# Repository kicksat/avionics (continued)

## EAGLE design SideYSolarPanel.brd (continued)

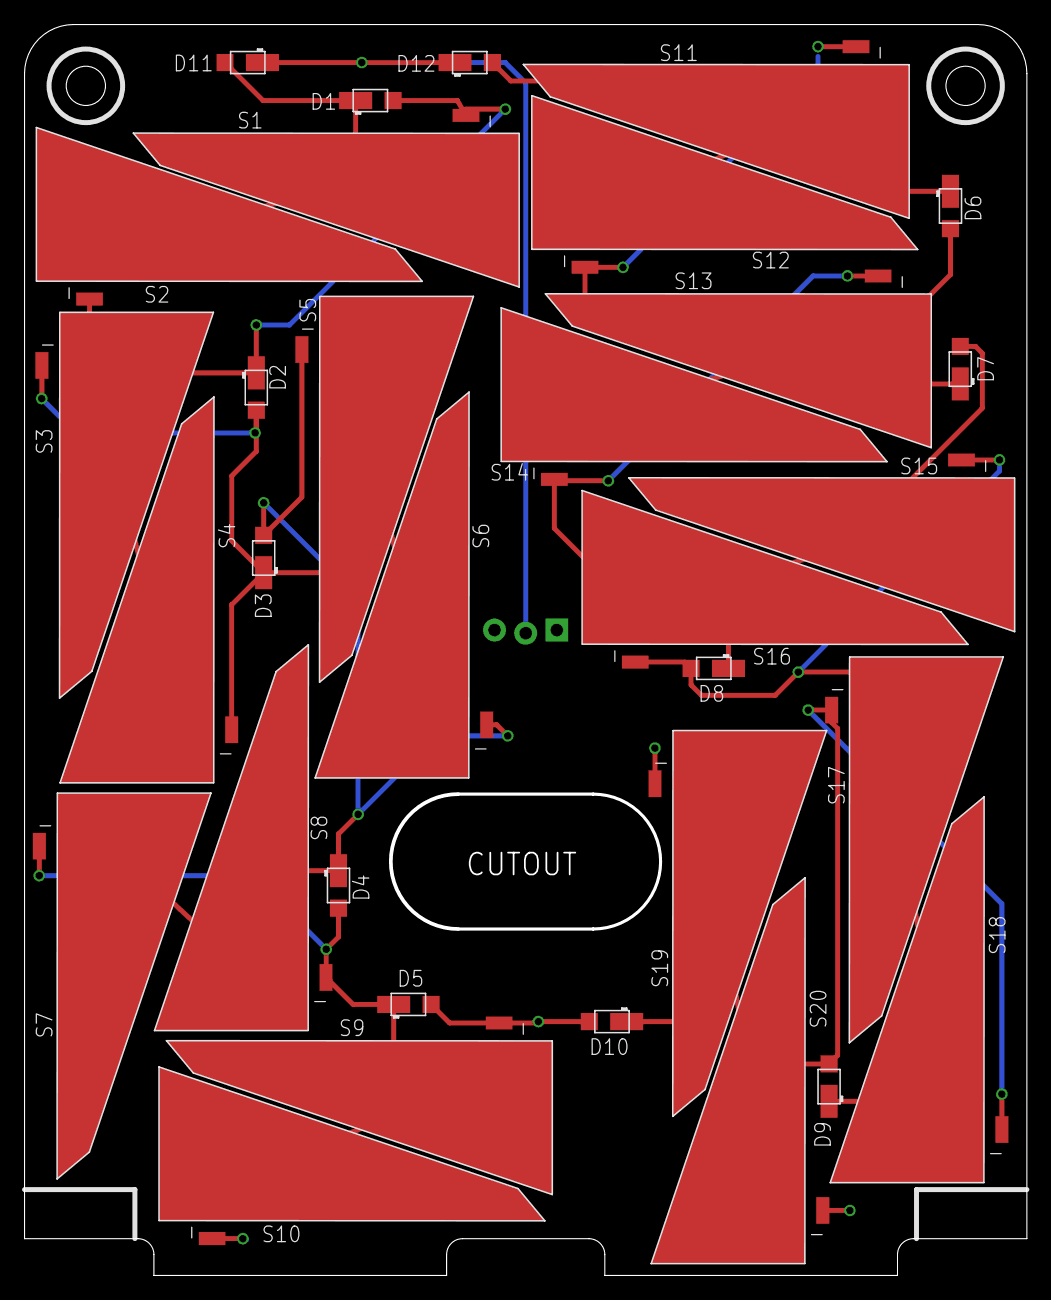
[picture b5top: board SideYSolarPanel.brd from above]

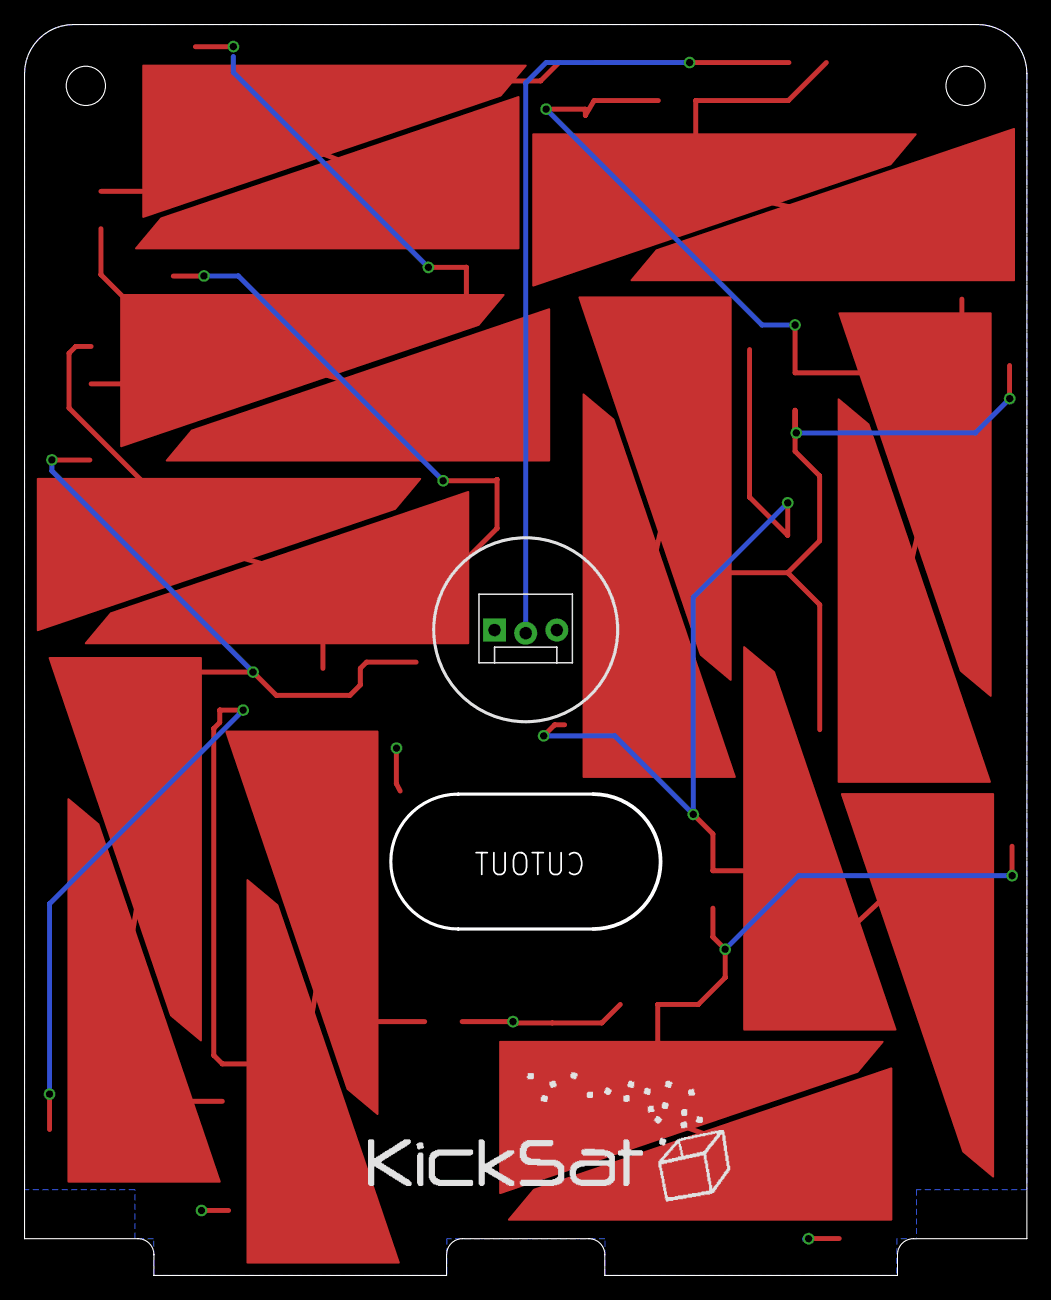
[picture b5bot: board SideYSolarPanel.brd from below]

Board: 2 copper layers, 81.7 x 102.0 mm, 35 parts (2 on the bottom side), 12 nets.

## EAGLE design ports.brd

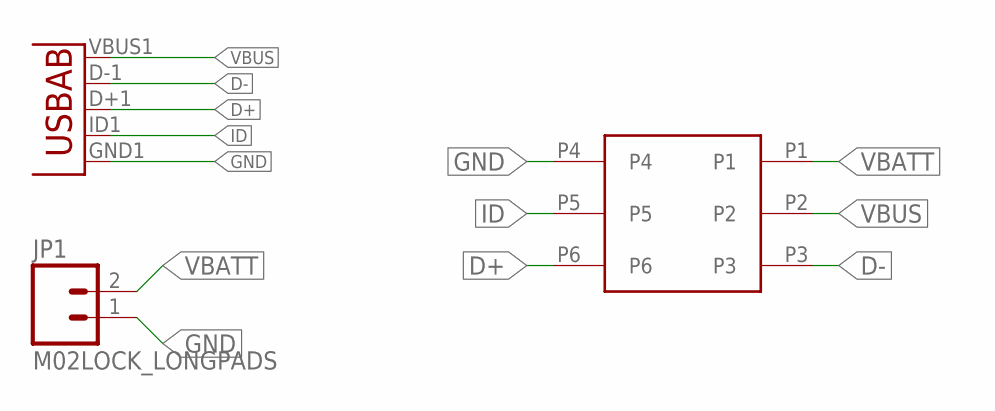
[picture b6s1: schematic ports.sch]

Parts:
JP1: M02LOCK_LONGPADS; 1X02_LOCK_LONGPADS
U$1: G125-FV20605L0P
U$4: USB-AB""; USB-AB-MICRO-SMD_V02_BOSS

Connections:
D+: U$1.P6, U$4.D+1 (D+)
D-: U$1.P3, U$4.D-1 (D-)
GND: JP1.1, U$1.P4, U$4.GND1 (GND)
ID: U$1.P5, U$4.ID1 (USBID)
VBATT: JP1.2, U$1.P1
VBUS: U$1.P2, U$4.VBUS1 (VBUS)

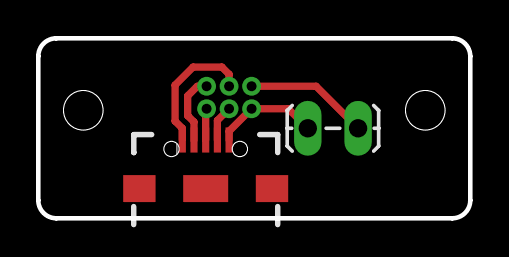
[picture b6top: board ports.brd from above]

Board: 2 copper layers, 24.0 x 10.0 mm, 3 parts (1 on the bottom side), 6 nets.

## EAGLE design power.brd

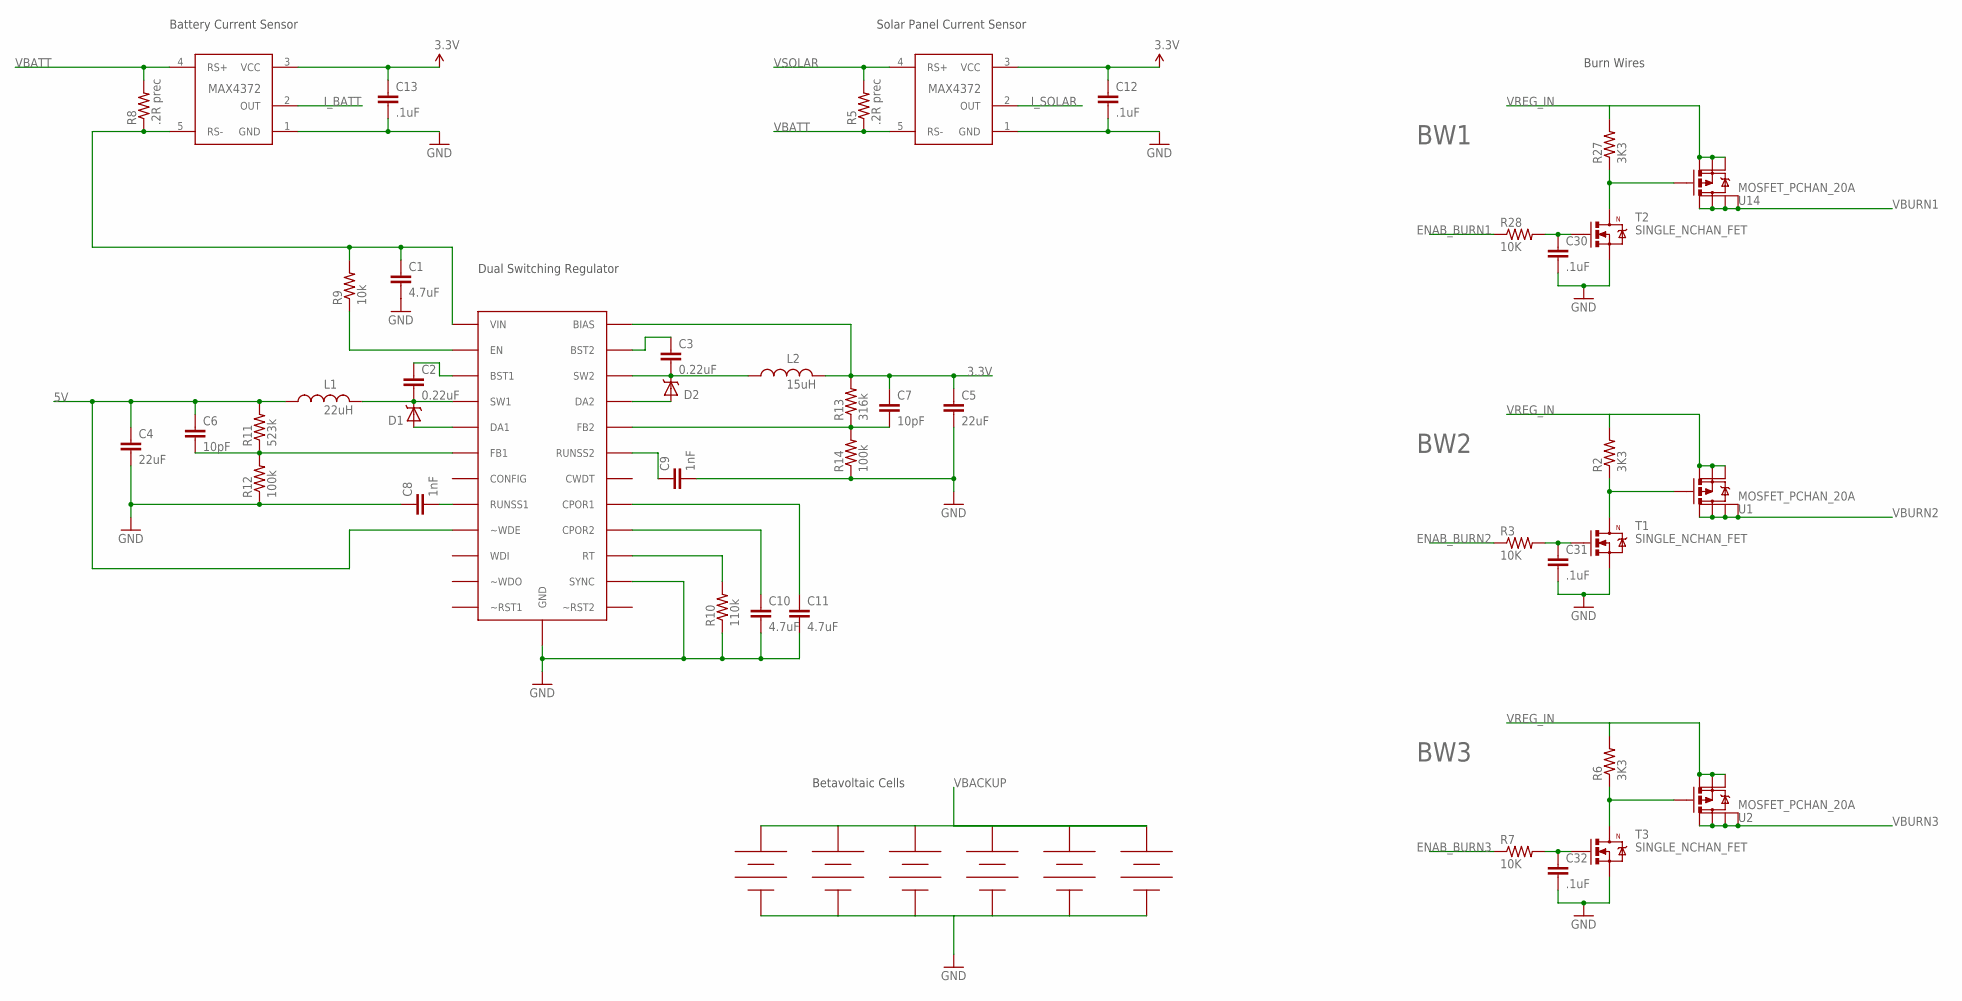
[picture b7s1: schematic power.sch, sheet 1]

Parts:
C1, C10, C11: 4.7uF; 0805
C2, C3: 0.22uF; 0805
C4, C5: 22uF; 1210
C6, C7: 10pF; 0805
C8, C9: 1nF; 0805
C12, C13, C30, C31, C32: .1uF; 0805
D1, D2: BAT20J; SOD-323
L1, L2: SLF10145
R2, R6, R27: 3K3; 0805
R3, R7, R28: 10K; 0805
R5, R8: .2R prec; 0805
R9: 10k; 0805
R10: 110k; 0805
R11: 523k; 0805
R12, R14: 100k; 0805
R13: 316k; 0805
T1, T2, T3: SINGLE_NCHAN_FET; SOT23-3
U1, U2, U14: MOSFET_PCHAN_20A; SO8
U$7, U$8, U$9, U$10, U$11, U$12: BETABATTERY
U$13: LT3688; LT3688TSSOP
U$14, U$15: CURRENT_MAX4372; SOT23-5

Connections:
3.3V: C5.1, C7.1, C12.1, C13.1, L2.P2, R13.2, U$13.BIAS, U$14.3 (VCC), U$15.3 (VCC); also elsewhere on the board
5V: C4.1, C6.1, L1.P1, R11.2, U$13.WDE (~WDE); also elsewhere on the board
ENAB_BURN1: R28.1
ENAB_BURN2: R3.1
ENAB_BURN3: R7.1
GND: C1.2, C4.2, C5.2, C8.1, C9.2, C10.2, C11.2, C12.2, C13.2, C30.2, C31.2, C32.2, R10.1, R12.1, R14.1, T1.2 (S), T2.2 (S), T3.2 (S), U$7.V-, U$8.V-, U$9.V-, U$10.V-, U$11.V-, U$12.V-, U$13.GND, U$13.SYNC, U$14.1 (GND), U$15.1 (GND); also elsewhere on the board
I_BATT: U$15.2 (OUT)
I_SOLAR: U$14.2 (OUT)
unnamed: C31.1, R3.2, T1.1 (G)
unnamed: R2.1, T1.3 (D), U1.4 (G)
unnamed: C32.1, R7.2, T3.1 (G)
unnamed: R6.1, T3.3 (D), U2.4 (G)
unnamed: R9.1, U$13.EN
unnamed: C9.1, U$13.RUNSS2
unnamed: C2.1, U$13.BST1
unnamed: C2.2, D1.C, L1.P2, U$13.SW1
unnamed: C3.1, U$13.BST2
unnamed: C6.2, R11.1, R12.2, U$13.FB1
unnamed: C8.2, U$13.RUNSS1
unnamed: C7.2, R13.1, R14.2, U$13.FB2
unnamed: C3.2, D2.C, L2.P1, U$13.SW2
unnamed: D1.A, U$13.DA1
unnamed: D2.A, U$13.DA2
unnamed: R10.2, U$13.RT
unnamed: C10.1, U$13.CPOR2
unnamed: C30.1, R28.2, T2.1 (G)
unnamed: C11.1, U$13.CPOR1
unnamed: R27.1, T2.3 (D), U14.4 (G)
VBACKUP: U$7.V+, U$8.V+, U$9.V+, U$10.V+, U$11.V+, U$12.V+; also elsewhere on the board
VBATT: R5.1, R8.2, U$14.5 (RS-), U$15.4 (RS+)
VBURN1: U14.5 (D), U14.6 (D), U14.7 (D), U14.8 (D); also elsewhere on the board
VBURN2: U1.5 (D), U1.6 (D), U1.7 (D), U1.8 (D); also elsewhere on the board
VBURN3: U2.5 (D), U2.6 (D), U2.7 (D), U2.8 (D); also elsewhere on the board
VREG_IN: C1.1, R2.2, R6.2, R8.1, R9.2, R27.2, U1.1 (S), U1.2 (S), U1.3 (S), U2.1 (S), U2.2 (S), U2.3 (S), U14.1 (S), U14.2 (S), U14.3 (S), U$13.VIN, U$15.5 (RS-); also elsewhere on the board
VSOLAR: R5.2, U$14.4 (RS+); also elsewhere on the board

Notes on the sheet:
BW1
BW2
BW3
22uH
15uH
Dual Switching Regulator
Betavoltaic Cells
Burn Wires
Solar Panel Current Sensor
Battery Current Sensor

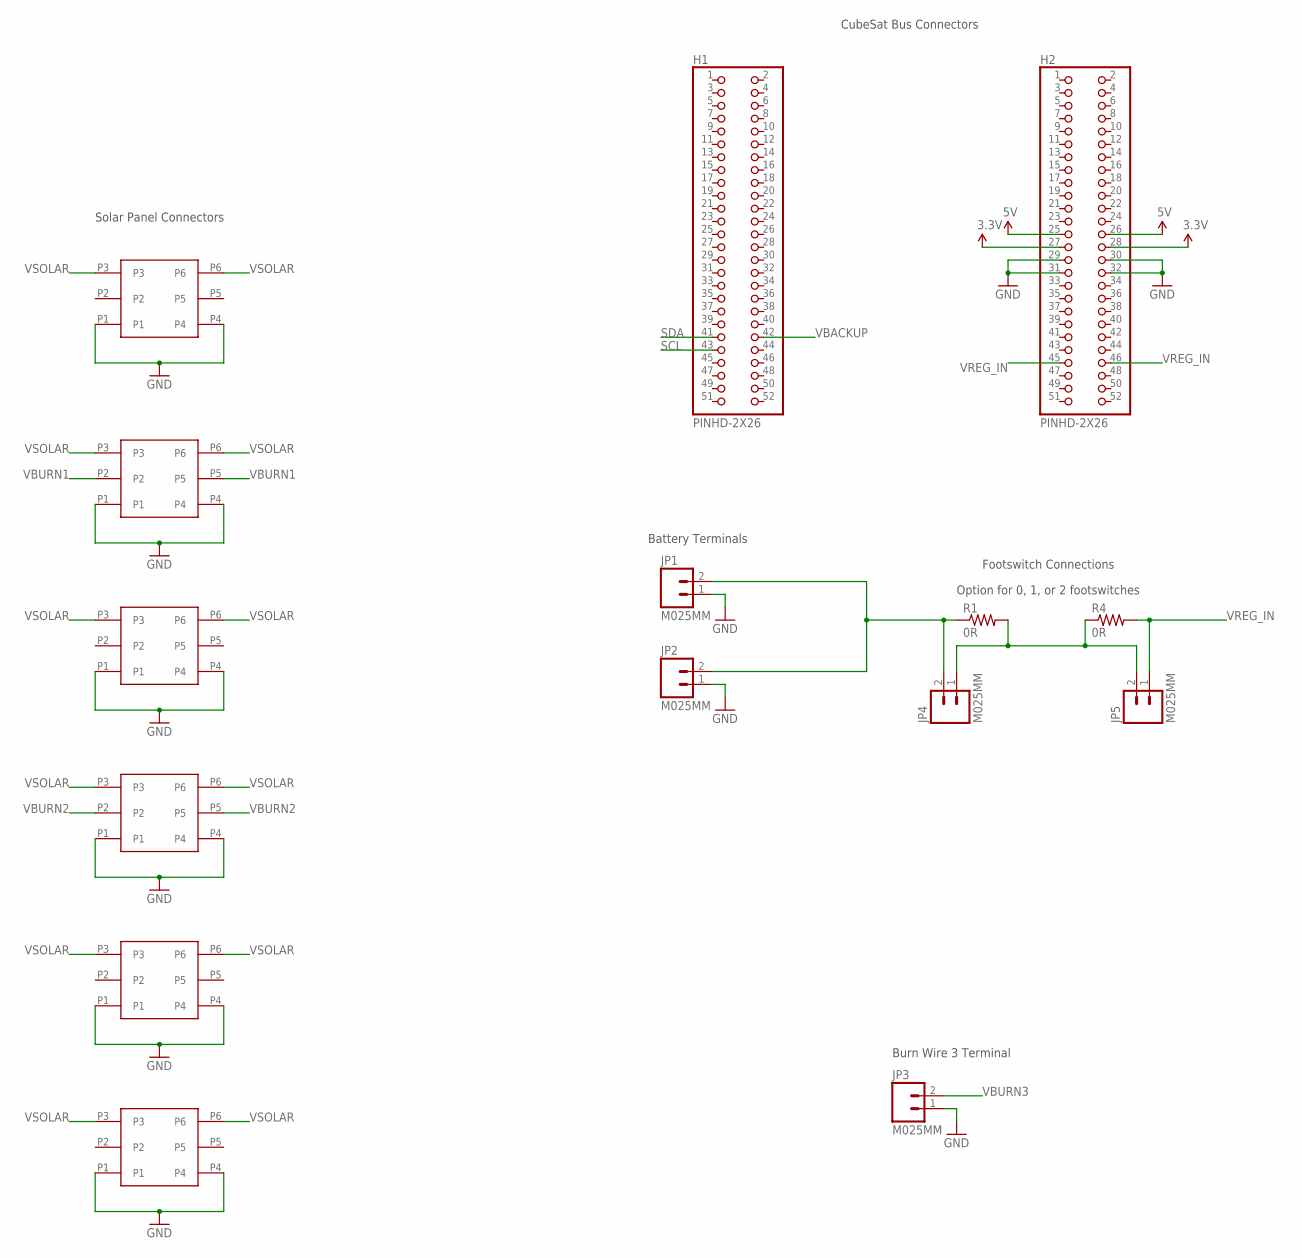
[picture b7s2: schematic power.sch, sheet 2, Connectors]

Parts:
H1, H2: PINHD-2X26; 2X26
JP1, JP2, JP3, JP4, JP5: M025MM; SCREWTERMINAL-5MM-2
R1, R4: 0R; R1210
U$1, U$2, U$3, U$4, U$5, U$6: G125-FV20605L0P

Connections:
3.3V: H2.27, H2.28; also elsewhere on the board
5V: H2.25, H2.26; also elsewhere on the board
BATT_INPUT: JP1.2, JP2.2, JP4.2, R1.1
GND: H2.29, H2.30, H2.31, H2.32, JP1.1, JP2.1, JP3.1, U$1.P1, U$1.P4, U$2.P1, U$2.P4, U$3.P1, U$3.P4, U$4.P1, U$4.P4, U$5.P1, U$5.P4, U$6.P1, U$6.P4; also elsewhere on the board
unnamed: JP4.1, JP5.2, R1.2, R4.1
SCL: H1.43
SDA: H1.41
VBACKUP: H1.42; also elsewhere on the board
VBURN1: U$6.P2, U$6.P5; also elsewhere on the board
VBURN2: U$1.P2, U$1.P5; also elsewhere on the board
VBURN3: JP3.2; also elsewhere on the board
VREG_IN: H2.45, H2.46, JP5.1, R4.2; also elsewhere on the board
VSOLAR: U$1.P3, U$1.P6, U$2.P3, U$2.P6, U$3.P3, U$3.P6, U$4.P3, U$4.P6, U$5.P3, U$5.P6, U$6.P3, U$6.P6; also elsewhere on the board

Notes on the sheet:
Footswitch Connections
Option for 0, 1, or 2 footswitches
Solar Panel Connectors
CubeSat Bus Connectors
Battery Terminals
Burn Wire 3 Terminal

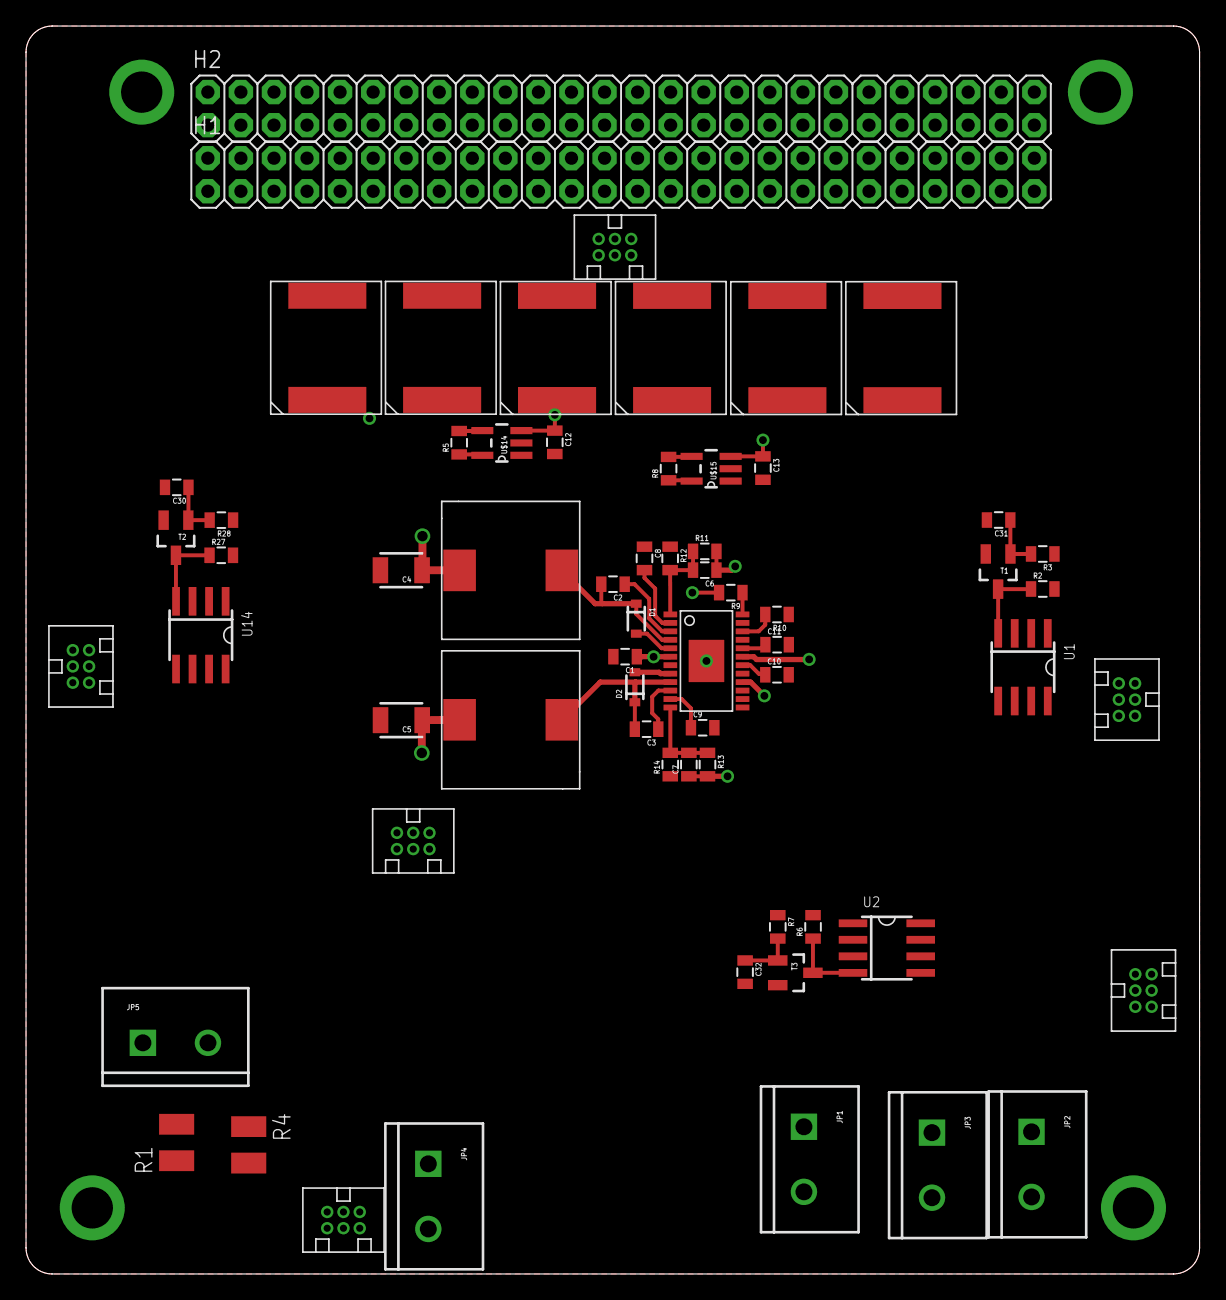
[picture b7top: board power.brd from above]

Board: 4 copper layers, 90.2 x 95.9 mm, 64 parts (0 on the bottom side), 32 nets.

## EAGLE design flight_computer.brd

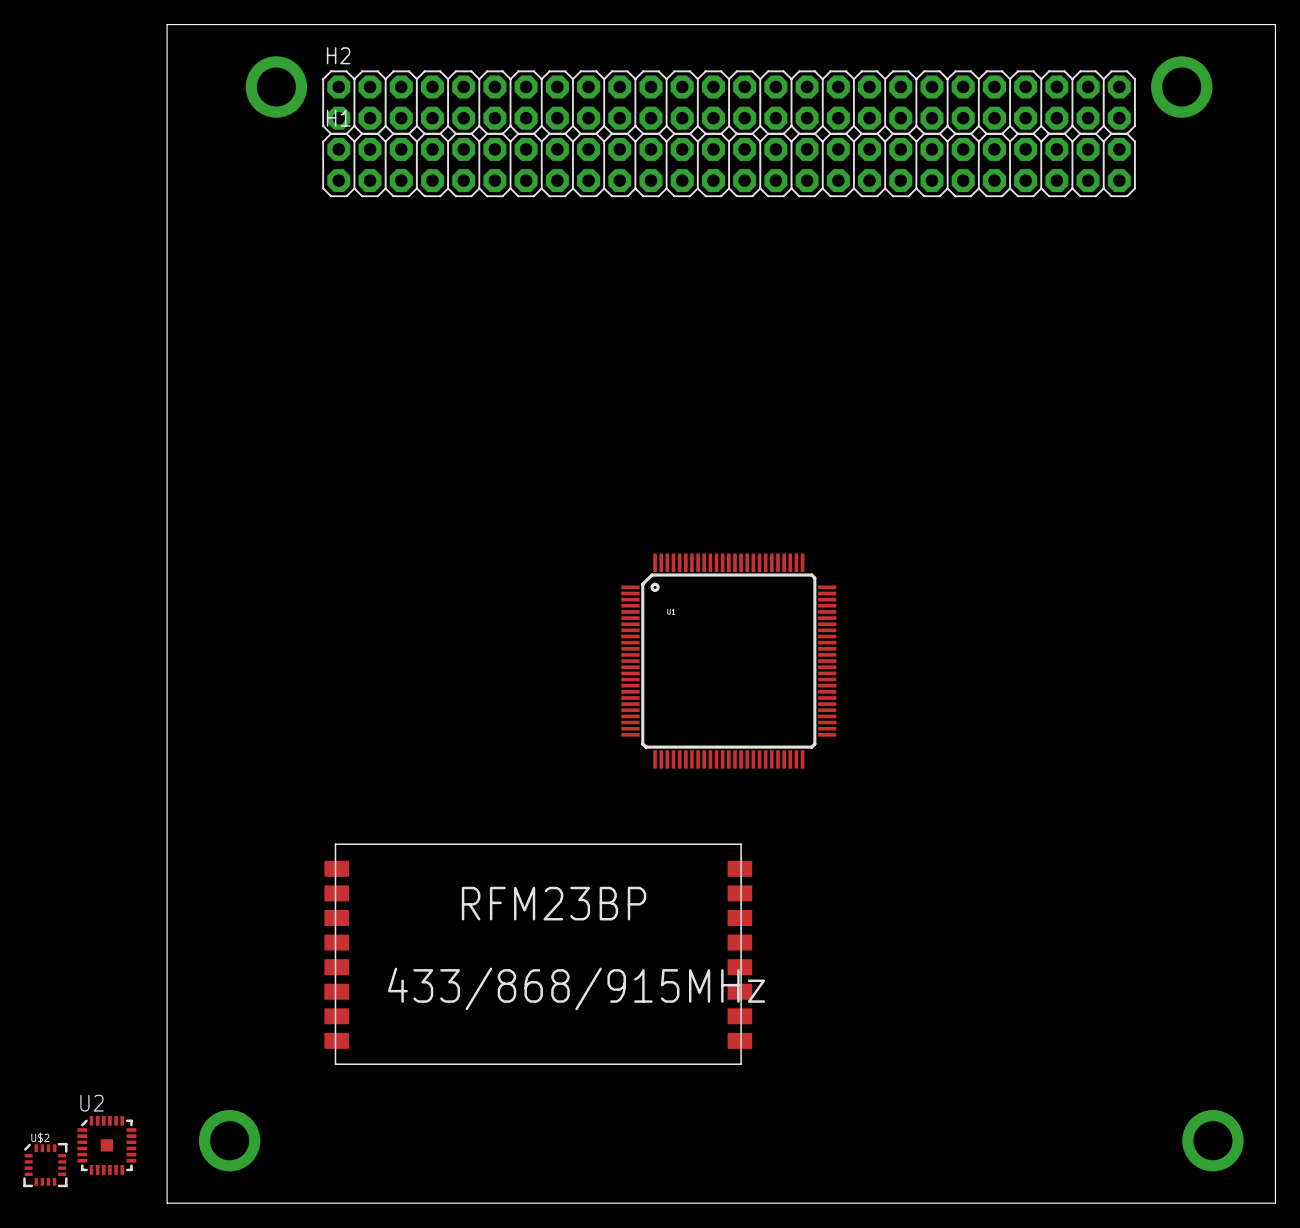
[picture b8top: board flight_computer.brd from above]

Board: 2 copper layers, 90.2 x 95.9 mm, 6 parts (0 on the bottom side), 4 nets, no tracks yet.

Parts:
H1, H2: PINHD-2X26; 2X26
U1: ATMEGA2560AU; TQFP100
U2: ITG-3200; QFN-24
U$1: RFM23BP
U$2: HMC5883LSMD; 16LPCC

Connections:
GND1: U1.32, U$1.GND1
GND2: U1.62, U$1.GND2
GND3: U1.81, U$1.GND3
VCC: U1.10, U$1.VCC

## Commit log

2014-06-02 Initial move
2014-06-02 rename main board
2014-06-05 Added documentation
2014-06-05 Newer datasheet
2014-06-19 Added libraries for balun and tape measure antenna
2014-06-20 Antenna layout
2014-06-23 changed antenna ground plane
2014-06-24 Positioned mounting holes on antenna board
2014-06-24 Antenna board silkscreen and gerbers
2014-06-25 Changed antenna board to 2 cutouts
2014-06-25 Mitered corners of mainboard
2014-06-25 Deleted old berbers
2014-06-25 Added level shifter
2014-07-01 Fixed silkscreen on antenna board
2014-07-01 Tweaks to antenna board
2014-07-02 Initial commit of power board
2014-07-08 Added RTC
2014-07-08 Added Micrel voltage supervisors
2014-07-09 Added new side solar panel
2014-07-11 Fixed manufacturing issue on TASC cell footprint
2014-07-21 Added latch-up protection circuits to main board
2014-07-22 Fixed solar panel issue
2014-07-22 Added solar panel libraries
2014-07-22 Added RTC backup batteries
2014-07-22 Power board work
2014-07-29 Added LT3688 dual regulator
2014-07-29 More switching regulator work
2014-07-29 Finished regulator circuit design
2014-07-30 Added foot switch terminals to power board
2014-07-30 Added current sensors to power board
2014-07-30 Changed to all sparkfun library parts
2014-08-01 Board layout for switching regulator
2014-08-01 More power board layout work
2014-08-11 Added breakout for USB and charging
2014-08-11 Removed silkscreen from gecko connector footprint
2014-08-11 Updated ports board
2014-08-11 Updated Gecko Connector
2014-08-11 Switching to teensy for flight computer
2014-08-12 Merged power and main board
2014-08-12 Mainboard layout work
2014-08-12 More layout work on main board
2014-08-12 Finished RTC schematic
2014-08-13 Got rid of level shifter for RF23BP
    Looks like it’s not necessary after some experimentation
2014-08-19 More layout work
2014-08-19 More layout work
    Changed radio + ska position to accomodate USB for teensy
2014-08-19 More main board layout
2014-08-19 Added OSHPark design rules
2014-08-20 main board layout work
2014-08-20 Finished main board layout
2014-08-20 Increased size of tape antenna solder pads
2014-08-21 Silkscreen Cleanup
2014-08-21 Added OSHPark Cam jobs + gerbers for main board
2014-08-21 Switched some components from 0603 to 0805
2014-08-21 Changed to 6mil tolerances
2014-08-21 Updated BOM with Digikey part numbers
2014-08-21 BOM Updates
2014-08-29 Widened copper around Gecko connector holes
2014-08-29 Move Gecko connector on ports board in from edge
2014-08-29 Fixed small silkscreen error
2014-09-09 Fixed burn wire
2014-09-09 Fixed solar panel silkscreen
2014-10-22 Beginning of new solar panel layout
    Changing to pairs of TASC cells to accommodate irregularities in
    dimensions
2014-10-23 Revert "New rev - cells in parallel"
    This reverts commit faff168c3f4bc65dfe0481fd6277a3f779fa2b6e.
2014-10-23 New rev - cells in parallel
2014-10-25 New side panel layout
2014-10-27 Revert 959c034..d13c0e4
    This rolls back to commit 959c03423f2cbd105642679eef46985d8f87b8b7.
2014-10-27 Fixed some schematic + layout issues on solar panel
    This reverts commit 959c03423f2cbd105642679eef46985d8f87b8b7.
    Conflicts:
    side_panel.brd
2014-10-27 Finished solar panel layout
2014-10-28 Changed silkscreen to bPlace layer on solar panel
2014-11-20 Swapped out power regulator
2014-12-05 Added solar cells to antenna board
2014-12-05 Updated side panel connectors
2015-01-14 Fixed silkscreen error
2015-08-21 Antenna board tweaks
    Changed connectors, fixed solar panel mirroring issue
2015-08-21 Antenna board connector fix
2015-08-21 Removed beta batteries
2015-08-24 New solar panel design
2015-08-28 Added "CUT OUT" text to cut outs
2015-08-28 Added OSH Park CAM files
2015-09-08 Updates to antenna board
    Fixed corner cutout dimensions. Added 3-pin Molex connector. Added
    “CUTOUT” text to dimension layer.
2015-09-08 Different X and Y side panels
2015-09-08 Change mounting hole diameter
2015-09-09 Solar panel layout work
2015-09-09 Finished routing X solar panel
2015-09-09 Moved screw holes on solar panel
2015-09-09 Finished routing Y solar panel
2015-09-09 Increased cutout line width
2015-09-10 Added pull down resistors to burn wire circuits
2015-09-10 Added stuff to mainboard for NanoRacks requirements
2015-09-11 Adding Arduino Pro Mini to Mainboard
2015-09-12 Added switches for programming mode
2015-09-12 Moved power connector
2015-09-14 Fixed charging jack on schematic
2015-09-14 DPDT Switch for programming mode
2015-09-14 Swapped X and Y solar panels per NanoRacks ICD
2015-09-15 added piksi gps connector and enable circuitry. Added molex library
2015-09-15 Schematic clean-up
2015-09-15 Mainboard routing work
2015-09-16 Some layout work
2015-09-17 Finished routing mainboard
2015-09-17 Added KickSat Logo
2015-09-17 Silkscreen Fix
2015-09-17 Cleanup
2015-09-17 Updated BOM
2015-09-22 Beginning of top solar panel
2015-09-22 Fixed solar cell footprints
2015-09-23 New top solar panel
2015-09-23 Updated read
2015-09-23 Changed antenna board to accommodate pumpkin clips
2015-09-23 Rename antenna.brd to Antenna.brd
2015-09-23 Rename antenna.sch to Antenna.sch
2015-09-23 Rename mainboard.brd to Mainboard.brd
2015-09-23 Rename mainboard.sch to Mainboard.sch
2015-09-23 Changed top board dimensions
2015-09-25 Adding pogo board
2015-09-25 Changed pogo board screws to M3
2015-10-05 Added license info
2015-11-01 Fixed bad trace on Y solar panel
2015-12-05 Changed R4 value on mainboard
2015-12-13 Added cap to battery voltage divider ADC input
2015-12-13 Changed voltage divider resistor values
2016-02-21 Trimmed corners of top solar panel
2017-02-05 Added battery voltage monitoring to arduino
2018-04-04 Added kicksat2 mainboard
    Took a snapshot of kicksat1 files, then added new mainboard schematic/layout/libraries
